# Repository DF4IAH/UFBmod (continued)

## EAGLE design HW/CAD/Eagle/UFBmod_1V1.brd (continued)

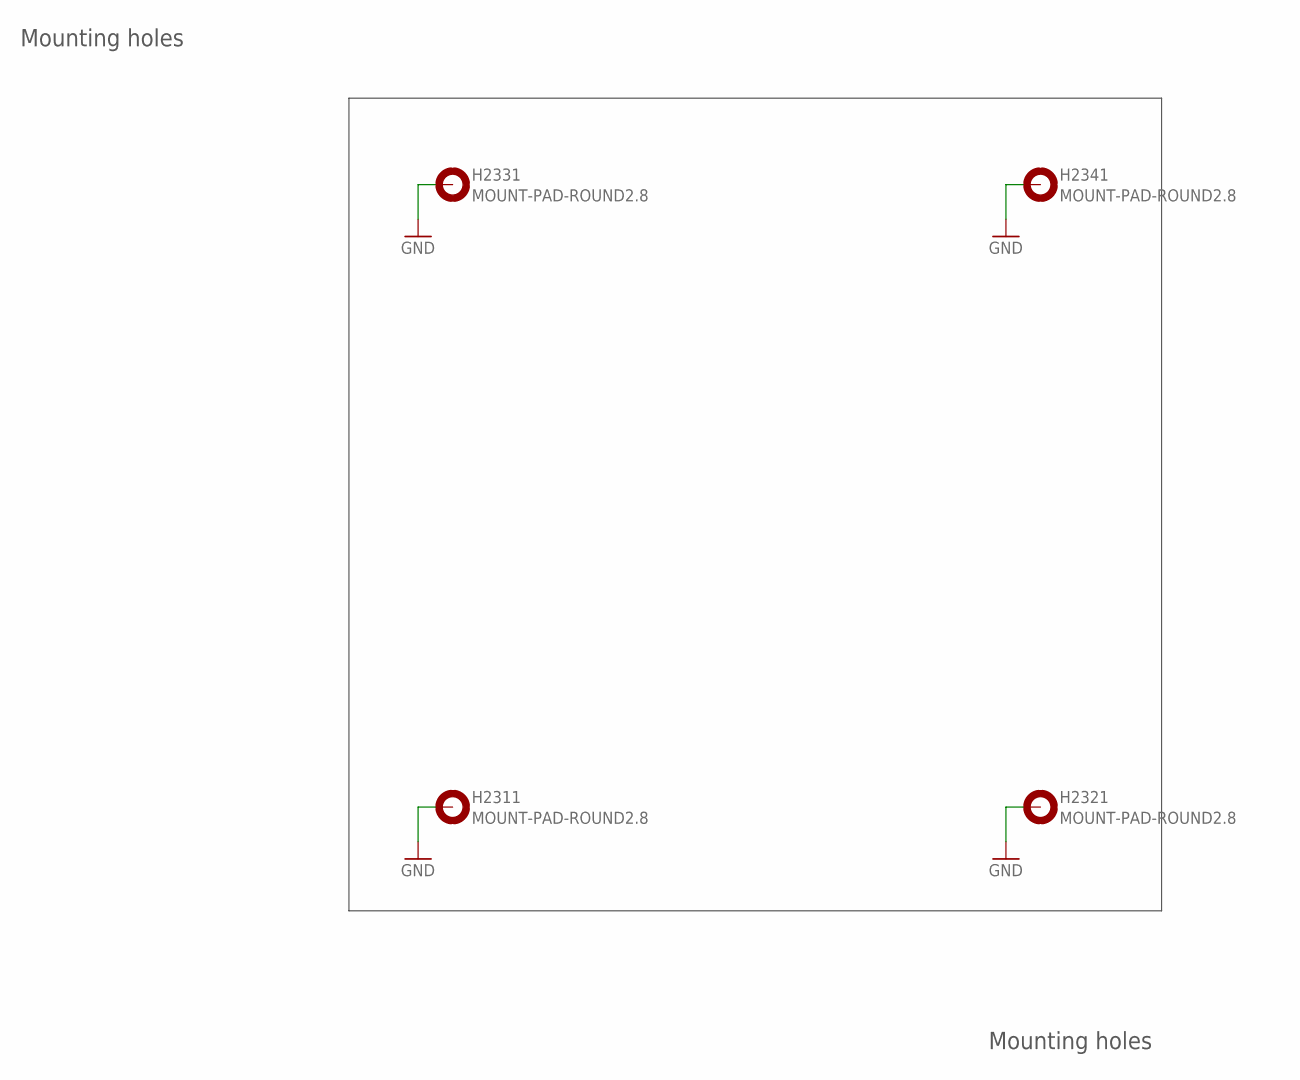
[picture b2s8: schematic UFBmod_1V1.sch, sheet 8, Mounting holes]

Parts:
H2311, H2321, H2331, H2341: MOUNT-PAD-ROUND2.8; 2,8-PAD

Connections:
GND: H2311.B2,8, H2321.B2,8, H2331.B2,8, H2341.B2,8; also elsewhere on the board

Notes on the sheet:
Mounting holes

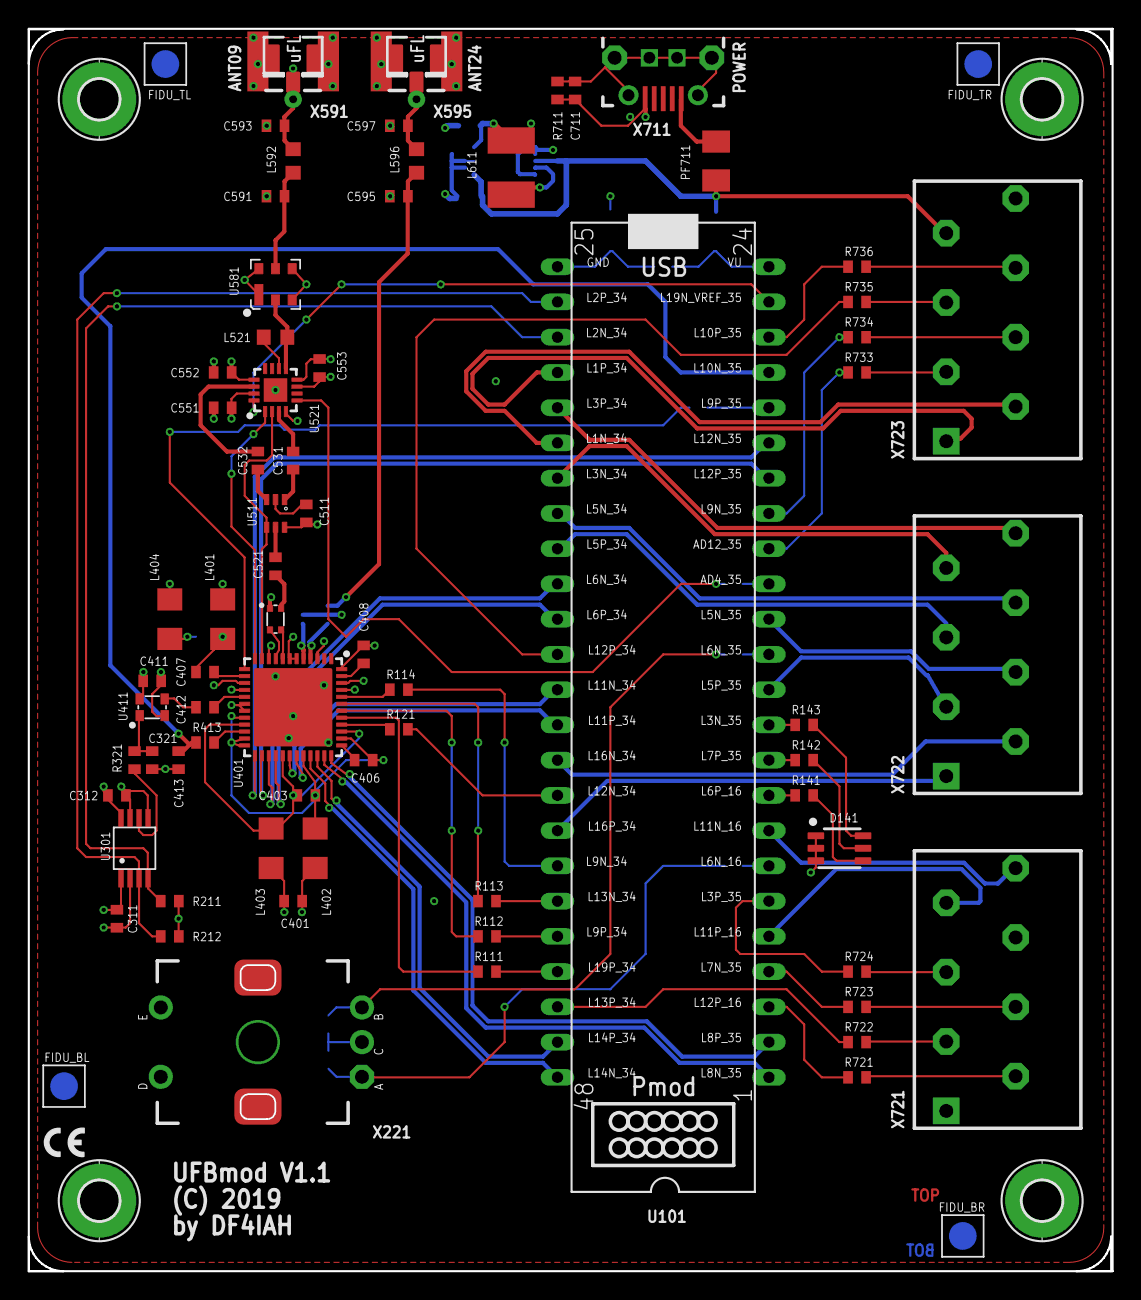
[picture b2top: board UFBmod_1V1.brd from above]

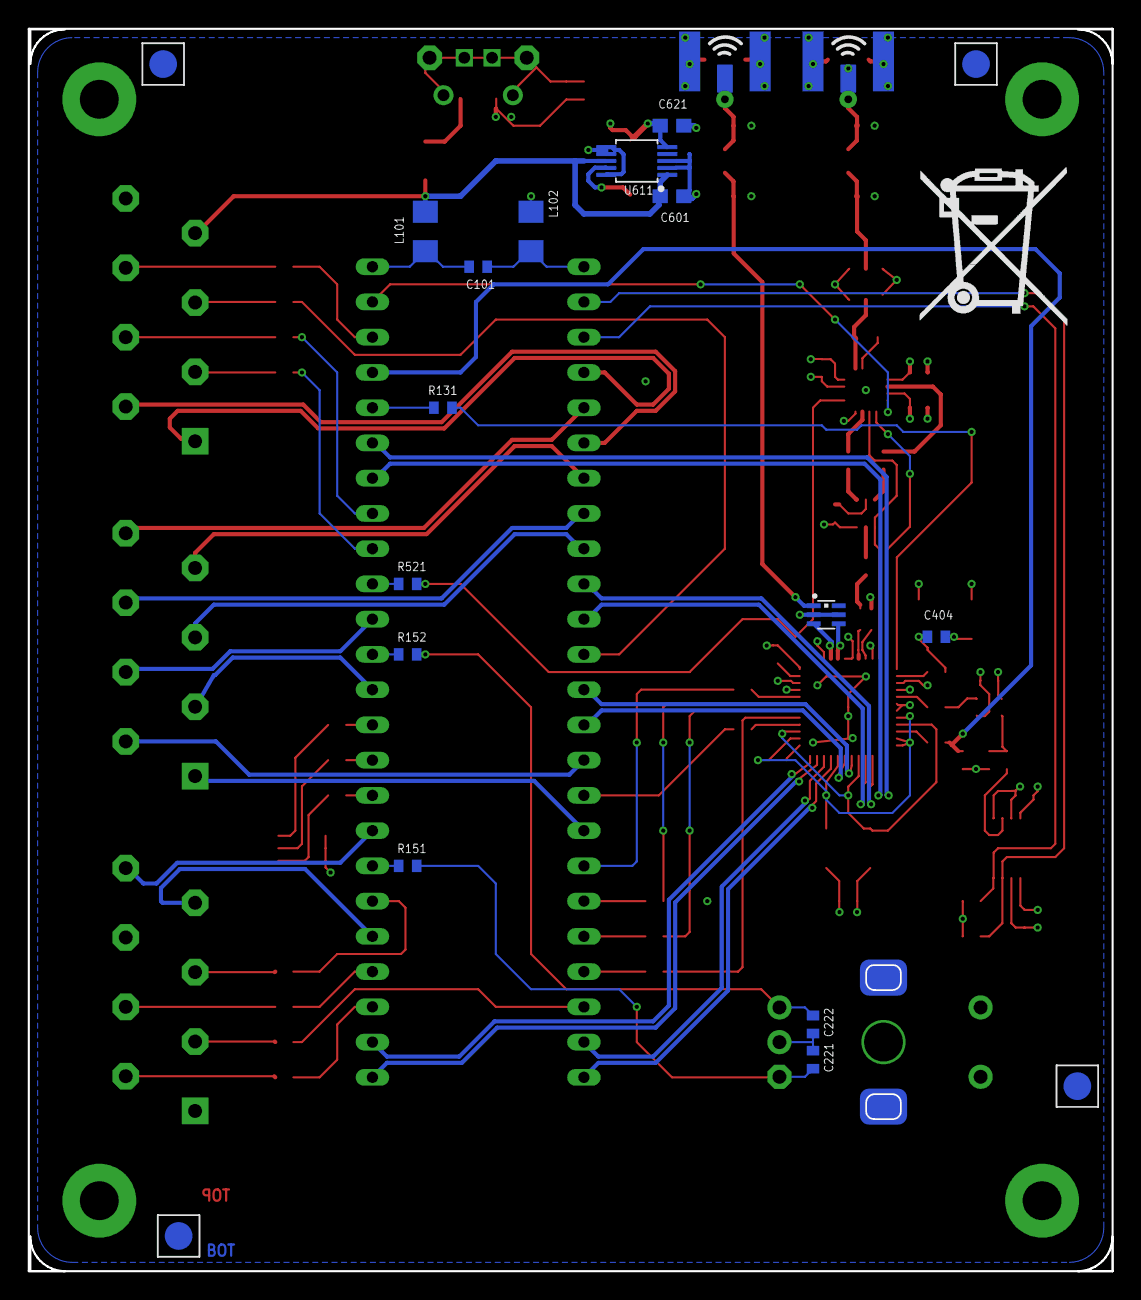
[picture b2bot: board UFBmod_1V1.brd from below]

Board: 4 copper layers, 78.1 x 89.5 mm, 91 parts (14 on the bottom side), 104 nets.

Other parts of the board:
FIDU_BL: FIDUCIAL_MARK_1MM
FIDU_BR: FIDUCIAL_MARK_1MM
FIDU_TL: FIDUCIAL_MARK_1MM
FIDU_TR: FIDUCIAL_MARK_1MM

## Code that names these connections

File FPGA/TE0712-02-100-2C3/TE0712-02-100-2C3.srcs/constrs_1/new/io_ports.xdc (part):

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#IO_L3N_T0_DQS_EMCCLK_14 sch:ONEWIRE


set_property -dict {PACKAGE_PIN T21 IOSTANDARD LVCMOS33} [get_ports fpga_lcd_bl_pwm]
#IO_L4P_T0_D04_14 sch:B14_L4_P --> FPGA_LCD_BL_PWM

set_property -dict {PACKAGE_PIN U21 IOSTANDARD LVCMOS33} [get_ports board_lcd_resetn]
#IO_L4N_T0_D05_14 sch:B14_L4_N --> BOARD_LCD_RESETN


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#IO_L7N_T1_D10_14 sch:ULI_SYSTEM


set_property -dict {PACKAGE_PIN AA20 IOSTANDARD LVCMOS33} [get_ports ddr3_init_calib_complete]
#IO_L8P_T1_D11_14 sch:B14_L8_P --> ddr3_init_calib_complete

#set_property -dict {PACKAGE_PIN AA21 IOSTANDARD LVCMOS33} [get_ports {b14_l8_n}]
#IO_L8N_T1_D12_14 sch:B14_L8_N


set_property -dict {PACKAGE_PIN Y21 IOSTANDARD LVCMOS33} [get_ports fpga_led_rgb_red]
#IO_L9P_T1_DQS_14 sch:B14_L9_P --> FPGA_LED_RGB_RED

set_property -dict {PACKAGE_PIN Y22 IOSTANDARD LVCMOS33} [get_ports fpga_led_rgb_green]
#IO_L9N_T1_DQS_D13_14 sch:B14_L9_N --> FPGA_LED_RGB_GREEN


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#IO_L12N_T1_MRCC_14 sch:B14_L12_N


set_property -dict {PACKAGE_PIN Y18 IOSTANDARD LVCMOS33} [get_ports board_rotenc_push]
#IO_L13P_T2_MRCC_14 sch:B14_L13_P --> BOARD_ROTENC_PUSH

#set_property -dict {PACKAGE_PIN Y19 IOSTANDARD LVCMOS33} [get_ports {b14_l13_n}]
#IO_L13N_T2_MRCC_14 sch:B14_L13_N


set_property -dict {PACKAGE_PIN V18 IOSTANDARD LVCMOS33} [get_ports board_rotenc_i]
#IO_L14P_T2_SRCC_14 sch:B14_L14_P --> BOARD_ROTENC_I

set_property -dict {PACKAGE_PIN V19 IOSTANDARD LVCMOS33} [get_ports board_rotenc_q]
#IO_L14N_T2_SRCC_14 sch:B14_L14_N --> BOARD_ROTENC_Q


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#IO_L16N_T2_A15_D31_14 sch:B14_L16_N


set_property -dict {PACKAGE_PIN AA18 IOSTANDARD LVCMOS33} [get_ports fpga_eth_da_y]
#IO_L17P_T2_A14_D30_14 sch:B14_L17_P --> FPGA_ETH_DA_Y

set_property -dict {PACKAGE_PIN AB18 IOSTANDARD LVCMOS33} [get_ports fpga_eth_da_g]
#IO_L17N_T2_A13_D29_14 sch:B14_L17_N --> FPGA_ETH_DA_G


set_property -dict {PACKAGE_PIN U17 IOSTANDARD LVCMOS33} [get_ports board_sda]
#IO_L18P_T2_A12_D28_14 sch:B14_L18_P --> BOAD_SDA

set_property -dict {PACKAGE_PIN U18 IOSTANDARD LVCMOS33} [get_ports board_scl]
#IO_L18N_T2_A11_D27_14 sch:B14_L18_N --> BOAD_SCL


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#set_property -dict {PACKAGE_PIN P16 IOSTANDARD LVCMOS33} [get_ports {b14_l24_p}]
#IO_L24P_T3_A01_D17_14 sch:B14_L24_P

set_property -dict {PACKAGE_PIN R17 IOSTANDARD LVCMOS33} [get_ports fpga_led_rgb_blue]
#IO_L24N_T3_A00_D16_14 sch:B14_L24_N --> FPGA_LED_RGB_BLUE


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#IO_L10N_T1_AD11N_15 sch:B15_L10_N


set_property -dict {PACKAGE_PIN J20 IOSTANDARD LVCMOS33} [get_ports trx_clk_26mhz]
#IO_L11P_T1_SRCC_15 sch:B15_L11_P --> TRX_CLK_26MHZ

#set_property -dict {PACKAGE_PIN J21 IOSTANDARD LVCMOS33} [get_ports {b15_l11_n}]
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
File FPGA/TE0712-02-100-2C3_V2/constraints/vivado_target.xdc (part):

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set_property IOSTANDARD LVCMOS33 [get_ports UART0_clk]


set_property PACKAGE_PIN AA20 [get_ports DDR3_init_calib_complete]
set_property IOSTANDARD LVCMOS33 [get_ports DDR3_init_calib_complete]


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set_property PACKAGE_PIN T21 [get_ports {LCD_BL}]
set_property IOSTANDARD LVCMOS33 [get_ports {LCD_BL}]

set_property PACKAGE_PIN Y21 [get_ports {LED_RGB_red}]
set_property IOSTANDARD LVCMOS33 [get_ports {LED_RGB_red}]

set_property PACKAGE_PIN Y22 [get_ports {LED_RGB_green}]
set_property IOSTANDARD LVCMOS33 [get_ports {LED_RGB_green}]

set_property PACKAGE_PIN R17 [get_ports {LED_RGB_blue}]
set_property IOSTANDARD LVCMOS33 [get_ports {LED_RGB_blue}]


set_property PACKAGE_PIN V18 [get_ports BOARD_ROTENC_I]
set_property IOSTANDARD LVCMOS33 [get_ports BOARD_ROTENC_I]
set_property PULLUP true [get_ports BOARD_ROTENC_I]

set_property PACKAGE_PIN V19 [get_ports BOARD_ROTENC_Q]
set_property IOSTANDARD LVCMOS33 [get_ports BOARD_ROTENC_Q]
set_property PULLUP true [get_ports BOARD_ROTENC_Q]

set_property PACKAGE_PIN Y18 [get_ports BOARD_ROTENC_PUSH]
set_property IOSTANDARD LVCMOS33 [get_ports BOARD_ROTENC_PUSH]
set_property PULLUP true [get_ports BOARD_ROTENC_PUSH]

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set_property IOSTANDARD LVCMOS33 [get_ports {TRX_rfx_mode}]


set_property PACKAGE_PIN J20 [get_ports TRX_clk_26MHz]
set_property IOSTANDARD LVCMOS33 [get_ports TRX_clk_26MHz]
set_property PULLDOWN true [get_ports TRX_clk_26MHz]

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
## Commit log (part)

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2019-07-29 FPGA - synthesize okay
2019-07-30 FPGA - Behav. simu okay, again
2019-07-30 FPGA - FTDI RX/TX added - implementation works
2019-07-30 FPGA - .gitignore and clean-up
2019-07-31 DOCS - FPGA - Artix-7 docs for timing
2019-07-31 FPGA - constraints - try more details
2019-08-01 FPGA - constraints - now much better set of constraints found
2019-08-02 FPGA - SERDES clock and reset fix
2019-08-02 FPGA - more fixes around LVDS block
2019-08-02 FPGA - new timing constraints
2019-08-02 FPGA - implementation state
2019-08-02 SW - first setup for SDK
2019-08-03 SW - remove, FPGA - QSPI added
2019-08-03 DOCS - FPGA - SDK tutorial added
2019-08-04 FPGA - Vivado2019.1 update
2019-08-04 FPGA - bind *.ELF files of the SDK, use PeriphTest for all BRAM init
2019-08-04 FPGA - SDK - do disassemble - result for PeriphTest
2019-08-04 DOCS - FPGA - mb_ref_guide.pdf added
2019-08-04 DOCS - FPGA - ds181 renamed
2019-08-04 FPGA - SDK - missing script added
2019-08-05 FPGA - Vivado2019.1.1 update
2019-08-06 HW - CAD/Eagle - update FPGA assignments
2019-08-08 HW_2V0 - CAD/Eagle - RESET button added
2019-08-08 FPGA - coding the ONEWIRE
2019-08-11 FPGA - Onewire - behavioral simulation and fixes
2019-08-11 FPGA - Onewire - BD update for other solution with DMA instead of register polling
2019-08-13 FPGA - Onewire - Schmerztag
2019-08-14 FPGA - Onewire - check SAK, check bittrain-counter +1
2019-08-15 FPGA - Onewire - synthesis okay, ethernet to connect ports
2019-08-17 FPGA - ELF file - non-valid file removed
2019-08-21 FPGA - Ethernet - BD okay
2019-08-22 HW_2V0 - CAD/Eagle - Ethernet Link-LED added
2019-08-22 FPGA - Ethernet - Implementation, bitfile done
2019-08-22 FPGA - clocks - refactoring
2019-08-23 FPGA - clocks - new setup
2019-08-25 HW_2V0 - CAD/Eagle - move all devices on the PCB area
2019-08-25 DOCS - 12_TrendzElectronic - ug* docs added
2019-08-25 FPGA - BD - re-creation works, mcu.tcl needed corrections
2019-08-26 FPGA - timing - tweaks done
2019-08-26 FPGA - timing - RTL analysis okay
2019-08-26 FPGA - timing - Check timing okay
2019-08-27 FPGA - timing - again optimized with Constr-Wizard
2019-08-27 FPGA - synthesis - DRC okay
2019-08-28 PGA - warnings and errors ... - giving up for today
2019-08-29 FPGA - timing - try these SETUP and HOLD times from the datasheets
2019-08-29 FPGA - BlockDesign - AXI-xbar refactored
2019-08-30 FPGA - SPI - use 25 MHz clock for both entities
2019-08-30 FPGA - timing - new way to solve timings better
2019-09-01 FPGA - BD - FFT unit now with CORDIC cart. --> polar
2019-09-01 FPGA - BD - FFT 4MSPS, 128 dots refactored
2019-09-02 FPGA - BD - missing source directory added
2019-09-03 FPGA - Behavioural simulation - checking LVDS_in SERDES (2)
2020-04-15 FPGA - remove old test-board dir
2020-04-15 FPGA - rename test_board to new own solution V2
2020-04-15 FPGA - V2 - after run of _create_win_setup.cmd
2020-04-15 FPGA - V2 - msys.pdf overview exported
2020-04-15 FPGA - V2 - synthesis and implementation done
2020-04-17 HW - Eagle - V1.0 title changed
2020-04-17 HW - Eagle - V2.0 title changed
2020-04-17 FPGA - V2 - schematic of implementation of the Trenz design added
2020-04-17 HW - Eagle - V2.1 update to current FPGA implementation
2020-04-18 gitignore - Eagle backup files added
2020-04-18 FPGA - V2 - UART0 complete, DDR3 complete - bitstream generated
2020-04-18 FPGA - V2 - ETH0 complete with status LEDs - bitstream generated
2020-04-18 FPGA - V2 - BOARD_I2C added - bitstream generated
2020-04-19 FPGA - V2 - ROTENC added - bitstream generated
2020-04-20 FPGA - V2 - missing PLL_int added - bitstream generated
2020-04-21 FPGA - V2 - TRX 26 MHz clock added - bitstream generated
2020-04-22 FPGA - V2 - FPGA_IO and ULI_SYSTEM input ports added - bitstream generated
2020-04-22 FPGA - V2 - TRX 26 MHz to 25 MHz extPLL added - bitstream generated (2)
2020-04-22 FPGA - V2 - LVDS interface to and from TRX added - bitstream generated
2020-04-23 FPGA - V2 - LVDS data handling until clock domain exchange added - bitstream generated
2020-04-24 FPGA - V2 - TRX RX FFT 4096 added - bitstream generated
2020-04-25 FPGA - V2 - bad BOARD_PIN(RESET) fixed - bitstream generated
2020-04-30 FPGA - V2 - BD build complete instead of sub-groups - bitstream generated
2020-05-01 FPGA - V2 - FuncSimu - fixes to get simu to start
2020-05-08 FPGA - V2 - FuncSimu - wrong stimulus fixed
2020-05-08 FPGA - V2 - FuncSimu - TRX_proc_sys_reset_0 fixed
2020-05-09 FPGA - V2 - FuncSimu - TRX LVDS reset fixed (2)
2020-05-09 FPGA - V2 - build complete after fixes - bitstream generated
2020-05-12 FPGA - V2 - FuncSimu - barrel rotator with testbench added
2020-05-13 FPGA - V2 - FuncSimu - auto barrel rotator fixed again
2020-05-13 FPGA - V2 - FuncSimu - grouped
2020-05-15 FPGA - V2 - Timing closures fixed, FFT missing - bitstream generated
2020-05-15 FPGA old *.dcp deleted
2020-05-15 FPGA - V2 - FFT included - bitstream generated (2)
2020-05-23 FPGA - V2 - FuncSimu - FFT Controller some issues solved - works
2020-05-24 FPGA - V2 - Synthesis - FFT-Controller VHDL fixed
2020-05-24 FPGA - V2 - TRX DDS (TX0/1) added in BD
2020-05-25 FPGA - V2 - TRX - bitfile generated
2020-05-27 HW_2V0 - CAD/Eagle - some more wires routed
2020-06-10 FPGA - V2 - Upgrade to Vivado2020.1
2020-06-12 HW_2V0 - CAD/Eagle - diff/uni RF net classes for ETH/LVDS and USB fixed
2020-06-12 HW_2V0 - CAD/Eagle - LVDS imp lines routed
2020-06-24 HW_2V1 - CAD/Eagle - initial routing done, ERC and DRC to follow
2020-06-25 HW_2V1 - CAD/Eagle - DRC work-of-the-day
2020-06-26 HW_2V1 - CAD/Eagle - some minor fixes
2020-06-27 FPGA - V2 - Export FPGA hardware info and bitstream
2020-06-27 SW - V2 - create new workspace for vitis (2)
2020-06-27 SW - V2 - create new workspace for vitis (4)
2020-06-27 DOCS - Energy usage coarse estimation
2020-06-27 SW - V2 - hello_world re-compiled
2020-07-01 HW - Eagle - V2.1a - bad switch in library fixed in schematic and board files
2020-07-01 DOCS - 12_TrenzElectronic - TE0712-02-100-2C3 fotos
2020-07-02 DOCS - 51_TRX - more TRX chips added (2)
2020-07-03 HW - Eagle - V2.1a - board house returned files again - but bad this time
2020-07-07 HW - Eagle - V2.1a - board house manufactured steps - photos added
2020-07-08 HW - Eagle - V2.1a - welcome of manufactured PCBs
2020-07-13 HW - Eagle - V2.2 - balun missing chip names and values added
2020-07-15 SW - V2 - FPGA: QSPI-Flash readout done.
2020-07-16 HW - Eagle - V2.2 - suppressor diodes for USB to be added
2020-07-16 FPGA - V2 - missing pull-ups added for ROTENC and more
2020-07-17 FPGA/SW - V2 - ROTENC fixed
2020-07-18 DOCS - 12_Trendz - spelling of PLL chip fixed
2020-07-18 DOCS - 31_LCD - MIDAS MCCOG21605B6W 16x2 added
2020-07-19 HW - Eagle - V2.2 - I2C address map fixed again
2020-07-19 HW - Eagle - V2.2 - font size changed for DAC and volt. reference
2020-07-20 FPGA - V2 - rework of ETH LEDs done
2020-07-20 FPGA/SW - V2 - rework of ETH unit done
2020-07-21 FPGA - V2 - rework of ETH unit for clocks, resets and monoflop for activity LED
2020-07-21 SW - V2 - refactoring Appl
2020-07-22 SW - V2 - RTOS: vTaskDelay() hangs
2020-07-22 Revert "Revert "SW - V1 - RTOS: vTaskDelay() hangs""
    This reverts commit b882dfe7e37ca2383065750671960088a4f45093.
2020-07-24 FPGA/SW - V2 - initial try to access EUI48
2020-07-27 FPGA/SW - V2 - still trying to decode ethernet traffic
2020-07-28 FPGA - V2 - SCOPE added, SCOPE_FSM still to write
2020-07-30 FPGA - V2 - SCOPE testbench added, SCOPE fixed
2020-08-01 FPGA/SW - V2 - USER OUT and CLK1B phase programmable for MII analysis
2020-08-05 FPGA - V2 - axi_ethernetlite DUT created - BehavSimu starts up
2020-08-05 FPGA/SW - V2 - ARP/ICMP Ping response works
2020-08-06 FPGA/SW - V2 - ETH LEDs green (link) and yellow (traffic) works
2020-08-06 FPGA - TE0712-02-100-2C3 (V1) - removed
2020-08-20 FPGA/SW - PLL boot-code using I2C IP for MicroBlaze #0 written, .elf file included
2020-08-21 FPGA/SW - BOOT and RTOS Soft-CPUs BRAM reduced to 16 kBytes each
2020-08-22 DOCS - 12_Trenz - Si5338 datasheets added
2020-08-22 FPGA/SW - I2C in boot_system works again
2020-08-23 FPGA/SW - SPI communication with the TRX works
2020-08-25 HW - Eagle - V2.1 V2.2 - TRX frontend pins configuration 1, not 2
2020-08-27 HW - Eagle - V2.1 V2.2 - TRX no 300R inductors at GND lines
2020-08-28 FPGA/SW - TRX I/Q calibration table done, FPGA DDS dual modulation mode works
2020-08-29 SW - TX - digital and analog front-end filters do not improve dBc value
2020-08-30 FPGA/SW - RX - LVDS works, XFFT shows energy when RF test signal is attached
2020-08-30 FPGA/SW - RX - RF24 LVDS working, also
2020-09-06 FPGA - TRX - TB added and multiple bugs in FFT_controller fixed
2020-09-08 FPGA - RX FFT - Hanning window included
2020-09-10 HW - Eagle - V2.1 V2.2 - Remarks for RF09 BALUN replacement
2020-09-14 FPGA - RX UFBmod Decoder - first try with Pre-FFT-Memory done, some good ideas are in it
2020-09-19 FPGA - RX UFBmod Decoder - synthesis to big with full width of 1024 points for the UFBmod_Decoder
2020-09-22 FPGA/SW - RX UFBmod Decoder - binaries latest tweaks, UFBmod_Decoder new code with 3 generation bit decoder with restoration
2020-09-26 FPGA - RX UFBmod Decoder - new method of preamble and symbol decoding
2020-09-28 FPGA - TX UFBmod Encoder - testbench expanded
2020-09-30 FPGA - TX UFBmod Encoder - first compilation
2020-10-03 SW/FPGA - TX UFBmod Encoder - DDS Im/Re mult works
2020-10-06 SW/FPGA - TX UFBmod Decoder - UNSIGNED instead of Integer is bad, needs 92% instead of 82% for synth
2020-10-07 SW/FPGA - TX UFBmod Decoder - revert UFBmod_Decoder.vhd to Integer and unparted FSM of b3092fdcf2f3cba31a6c63433d2ed1063738a73e
2020-10-13 FPGA - TX UFBmod Decoder - setting up decoder with block-RAMs and mults
2020-10-14 FPGA - RX UFBmod Decoder - preamble 1 included to FSM
2020-10-18 FPGA - RX UFBmod Decoder - Artemis preamble searcher done
2020-10-20 FPGA - RX UFBmod Decoder - Artemis preamble hunter now SNR better than -20 dB
2020-10-20 FPGA - RX UFBmod Decoder - new BD for UFBmod_Decoder.bd
2020-10-20 FPGA - RX UFBmod Encoder - cleanup done
2020-10-21 FPGA - RX UFBmod Decoder - syntax error removed
2020-10-21 FPGA - RX UFBmod Decoder - row selection bug fixed
2020-10-22 FPGA - RX UFBmod Decoder/Encoder - symbols definition fixed
2020-10-22 FPGA - RX UFBmod Decoder - first set-up of data decoder with single symbol jump
2020-10-23 FPGA - RX UFBmod Decoder - single-bit dBc tests finished, now double-bit comes
2020-10-24 FPGA - RX UFBmod Decoder - preamble: using new constants
2020-10-26 FPGA - RX UFBmod Encoder/Decoder - connections to msys established
2020-10-27 FPGA - RX UFBmod Decoder - fix of message length
2020-10-28 FPGA - refactoring msys and extract top module
2020-10-29 FPGA - UFBmod_Decoder - FIFO connection added
2020-11-01 FPGA - UFBmod_Decoder - debugging the chXX instance done
2020-11-02 FPGA - top - renaming of signals done
2020-11-03 FPGA - UFBmod_Decoder - implementation minor fixes done
2020-11-04 FPGA - UFBmod_Decoder - configuration top.bit built
2020-11-05 FPGA/SW - first SREC load of rtos.srec
2020-11-09 FPGA - auto_LVDS_rotate - bugs fixed
2020-11-17 SW - SREC - multiple solutions for access the QSPI device: xilisf, xspi and direct QSPI device register access
2020-11-17 FPGA - SREC - current state (not yet working design)
2020-11-23 FPGA - SREC - against test-bench works
2020-11-24 FPGA - SREC - minor fixes
2020-12-02 FPGA/SW - SREC - debugging FSM
2021-01-10 HW - Eagle - V2.1 V2.2 - PMIC values changed for lower swing at VFB and OV-protection
2021-01-10 FPGA/SW - re-do compilations
2021-03-01 SW - DF4IAH_create_SREC.bat does chop off first line
2021-03-09 FPGA - SREC - after some more fixes - FPGA SREC bootloader works!!!
2021-03-09 HW - EAGLE - update eagle.epf
2021-03-10 FPGA - reduced debugging aids - booting works
2021-03-11 FPGA - reseating - new configuration for better reseating
2021-03-13 SW - update Vitis 2020.2 - workspace update
2021-03-16 SW - LCD - top menu handling works
2021-03-17 SW - LCD - navigation HF1 V01 added
2021-04-04 SW - LCD - some fixes with cursor positioning
2021-04-09 HW - EAGLE - V2.2 devices placed
2021-04-30 FPGA/SW - ROTENC counter fixes again, enabled RF output
